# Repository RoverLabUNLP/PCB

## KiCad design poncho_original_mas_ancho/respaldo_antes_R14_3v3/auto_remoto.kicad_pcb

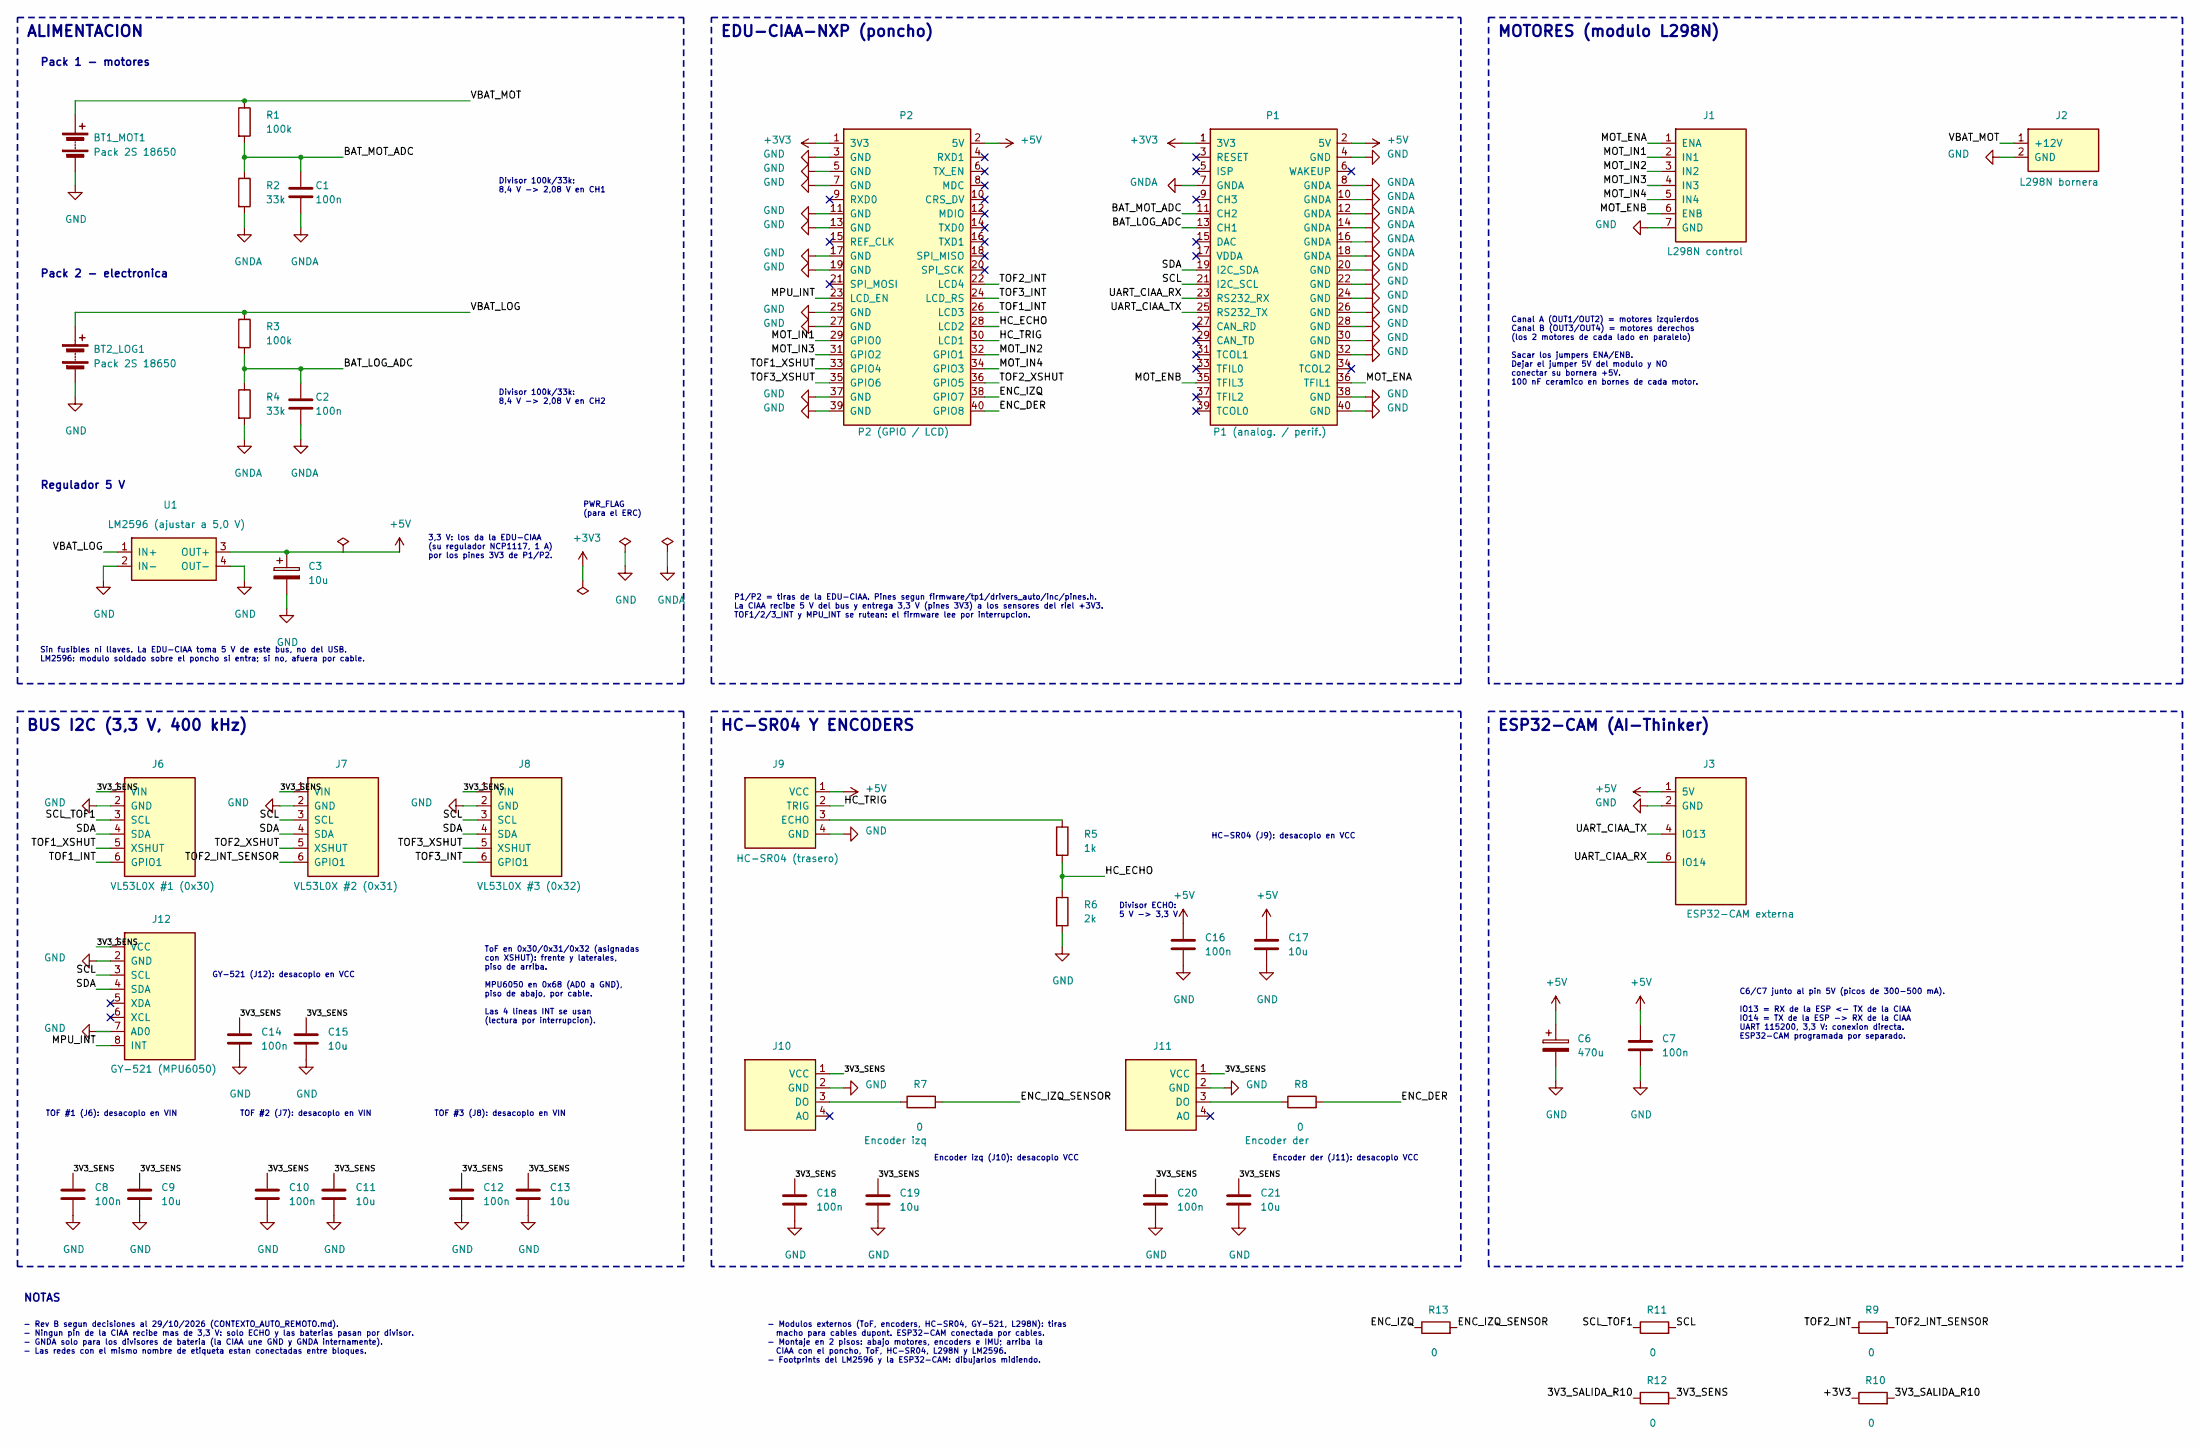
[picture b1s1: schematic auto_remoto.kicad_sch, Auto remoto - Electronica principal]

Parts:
BT1_MOT1, BT2_LOG1: Pack 2S 18650; Bornera_2_P5.00
C1, C2, C7, C8, C10, C12, C14, C16, C18, C20: 100n; C_P5.00
C3: 10u; CP_D6.3_P2.50
C6: 470u; CP_D6.3_P2.50
C9, C11, C13, C15, C17, C19, C21: 10u; C_P5.00
J1: L298N control; Tira_1x07
J2: L298N bornera; Bornera_2_P5.00
J3: ESP32-CAM externa; Pads_ESP32_CAM
J6: VL53L0X #1 (0x30); Tira_1x06
J7: VL53L0X #2 (0x31); Tira_1x06
J8: VL53L0X #3 (0x32); Tira_1x06
J9: HC-SR04 (trasero); Tira_1x04
J10: Encoder izq; Tira_1x04
J11: Encoder der; Tira_1x04
J12: GY-521 (MPU6050); Tira_1x08
P1: P1 (analog. / perif.); Tira_2x20_CIAA_P1
P2: P2 (GPIO / LCD); Tira_2x20_CIAA_P2
R1, R3: 100k; R_P10.16
R2, R4: 33k; R_P10.16
R5: 1k; R_P10.16
R6: 2k; R_P10.16
R7, R8, R9, R10, R11, R12, R13: 0; R_P10.16
U1: LM2596 (ajustar a 5,0 V); Modulo_LM2596

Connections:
+3V3: P1.1 (3V3), P2.1 (3V3), R10.1
+5V: C3.1, C6.1, C7.1, C16.1, C17.1, J3.1 (5V), J9.1 (VCC), P1.2 (5V), P2.2 (5V), U1.3 (OUT+)
/3V3_SALIDA_R10: R10.2, R12.1
/3V3_SENS: C8.1, C9.1, C10.1, C11.1, C12.1, C13.1, C14.1, C15.1, C18.1, C19.1, C20.1, C21.1, J6.1 (VIN), J7.1 (VIN), J8.1 (VIN), J10.1 (VCC), J11.1 (VCC), J12.1 (VCC), R12.2
/BAT_LOG_ADC: C2.1, P1.13 (CH1), R3.2, R4.1
/BAT_MOT_ADC: C1.1, P1.11 (CH2), R1.2, R2.1
/ENC_DER: P2.40 (GPIO8), R8.2
/ENC_IZQ: P2.38 (GPIO7), R13.1
/ENC_IZQ_SENSOR: R7.2, R13.2
/HC_ECHO: P2.28 (LCD2), R5.2, R6.1
/HC_TRIG: J9.2 (TRIG), P2.30 (LCD1)
/MOT_ENA: J1.1 (ENA), P1.36 (TFIL1)
/MOT_ENB: J1.6 (ENB), P1.35 (TFIL3)
/MOT_IN1: J1.2 (IN1), P2.29 (GPIO0)
/MOT_IN2: J1.3 (IN2), P2.32 (GPIO1)
/MOT_IN3: J1.4 (IN3), P2.31 (GPIO2)
/MOT_IN4: J1.5 (IN4), P2.34 (GPIO3)
/MPU_INT: J12.8 (INT), P2.23 (LCD_EN)
/SCL: J7.3 (SCL), J8.3 (SCL), J12.3 (SCL), P1.21 (I2C_SCL), R11.2
/SCL_TOF1: J6.3 (SCL), R11.1
/SDA: J6.4 (SDA), J7.4 (SDA), J8.4 (SDA), J12.4 (SDA), P1.19 (I2C_SDA)
/TOF1_INT: J6.6 (GPIO1), P2.26 (LCD3)
/TOF1_XSHUT: J6.5 (XSHUT), P2.33 (GPIO4)
/TOF2_INT: P2.22 (LCD4), R9.1
/TOF2_INT_SENSOR: J7.6 (GPIO1), R9.2
/TOF2_XSHUT: J7.5 (XSHUT), P2.36 (GPIO5)
/TOF3_INT: J8.6 (GPIO1), P2.24 (LCD_RS)
/TOF3_XSHUT: J8.5 (XSHUT), P2.35 (GPIO6)
/UART_CIAA_RX: J3.6 (IO14), P1.23 (RS232_RX)
/UART_CIAA_TX: J3.4 (IO13), P1.25 (RS232_TX)
/VBAT_LOG: BT2_LOG1.1 (+), R3.1, U1.1 (IN+)
/VBAT_MOT: BT1_MOT1.1 (+), J2.1 (+12V), R1.1
GND: BT1_MOT1.2 (-), BT2_LOG1.2 (-), C3.2, C6.2, C7.2, C8.2, C9.2, C10.2, C11.2, C12.2, C13.2, C14.2, C15.2, C16.2, C17.2, C18.2, C19.2, C20.2, C21.2, J1.7 (GND), J2.2 (GND), J3.2 (GND), J6.2 (GND), J7.2 (GND), J8.2 (GND), J9.4 (GND), J10.2 (GND), J11.2 (GND), J12.2 (GND), J12.7 (AD0), P1.4 (GND), P1.20 (GND), P1.22 (GND), P1.24 (GND), P1.26 (GND), P1.28 (GND), P1.30 (GND), P1.32 (GND), P1.38 (GND), P1.40 (GND), P2.3 (GND), P2.5 (GND), P2.7 (GND), P2.11 (GND), P2.13 (GND), P2.17 (GND), P2.19 (GND), P2.25 (GND), P2.27 (GND), P2.37 (GND), P2.39 (GND), R6.2, U1.2 (IN-), U1.4 (OUT-)
GNDA: C1.2, C2.2, P1.7 (GNDA), P1.8 (GNDA), P1.10 (GNDA), P1.12 (GNDA), P1.14 (GNDA), P1.16 (GNDA), P1.18 (GNDA), R2.2, R4.2
unnamed: J9.3 (ECHO), R5.1
unnamed: J10.3 (DO), R7.1
unnamed: J11.3 (DO), R8.1

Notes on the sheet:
Encoder izq (J10): desacoplo VCC
Regulador 5 V
HC-SR04 (J9): desacoplo en VCC
MOTORES (modulo L298N)
Pack 2 - electronica
ESP32-CAM (AI-Thinker)
HC-SR04 Y ENCODERS
GY-521 (J12): desacoplo en VCC
Divisor 100k/33k: 8,4 V -> 2,08 V en CH1
PWR_FLAG (para el ERC)
Encoder der (J11): desacoplo VCC
Sin fusibles ni llaves. La EDU-CIAA toma 5 V de este bus, no del USB. LM2596: modulo soldado sobre el poncho si entra; si no, afuera por cable.
BUS I2C (3,3 V, 400 kHz)
TOF #3 (J8): desacoplo en VIN
Pack 1 - motores
3,3 V: los da la EDU-CIAA (su regulador NCP1117, 1 A) por los pines 3V3 de P1/P2.
TOF #2 (J7): desacoplo en VIN
C6/C7 junto al pin 5V (picos de 300-500 mA). IO13 = RX de la ESP <- TX de la CIAA IO14 = TX de la ESP -> RX de la CIAA UART 115200, 3,3 V: conexion directa. ESP32-CAM programada por separado.
EDU-CIAA-NXP (poncho)
- Rev B segun decisiones al 29/10/2026 (CONTEXTO_AUTO_REMOTO.md). - Ningun pin de la CIAA recibe mas de 3,3 V: solo ECHO y las baterias pasan por divisor. - GNDA solo para los divisores de bateria (la CIAA une GND y GNDA internamente). - Las redes con el mismo nombre de etiqueta estan conectadas en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
NOTAS
ALIMENTACION
Divisor ECHO: 5 V -> 3,3 V
P1/P2 = tiras de la EDU-CIAA. Pines segun firmware/tp1/drivers_auto/inc/pines.h. La CIAA recibe 5 V del bus y entrega 3,3 V (pines 3V3) a los sensores del riel +3V3. TOF1/2/3_INT y MPU_INT se rutean: el firmware lee por interrupcion.
- Modulos externos (ToF, encoders, HC-SR04, GY-521, L298N): tiras macho para cables dupont. ESP32-CAM conectada por cables. - Montaje en 2 pisos: abajo motores, encoders e IMU; arriba la CIAA con el poncho, ToF, HC-SR04, L298N y LM2596. - Footprints del LM2596 y la ESP32-CAM: dibujarlos midiendo.
TOF #1 (J6): desacoplo en VIN
Divisor 100k/33k: 8,4 V -> 2,08 V en CH2
Canal A (OUT1/OUT2) = motores izquierdos Canal B (OUT3/OUT4) = motores derechos (los 2 motores de cada lado en paralelo) Sacar los jumpers ENA/ENB. Dejar el jumper 5V del modulo y NO conectar su bornera +5V. 100 nF ceramico en bornes de cada motor.
ToF en 0x30/0x31/0x32 (asignadas con XSHUT): frente y laterales, piso de arriba. MPU6050 en 0x68 (AD0 a GND), piso de abajo, por cable. Las 4 lineas INT se usan (lectura por interrupcion).

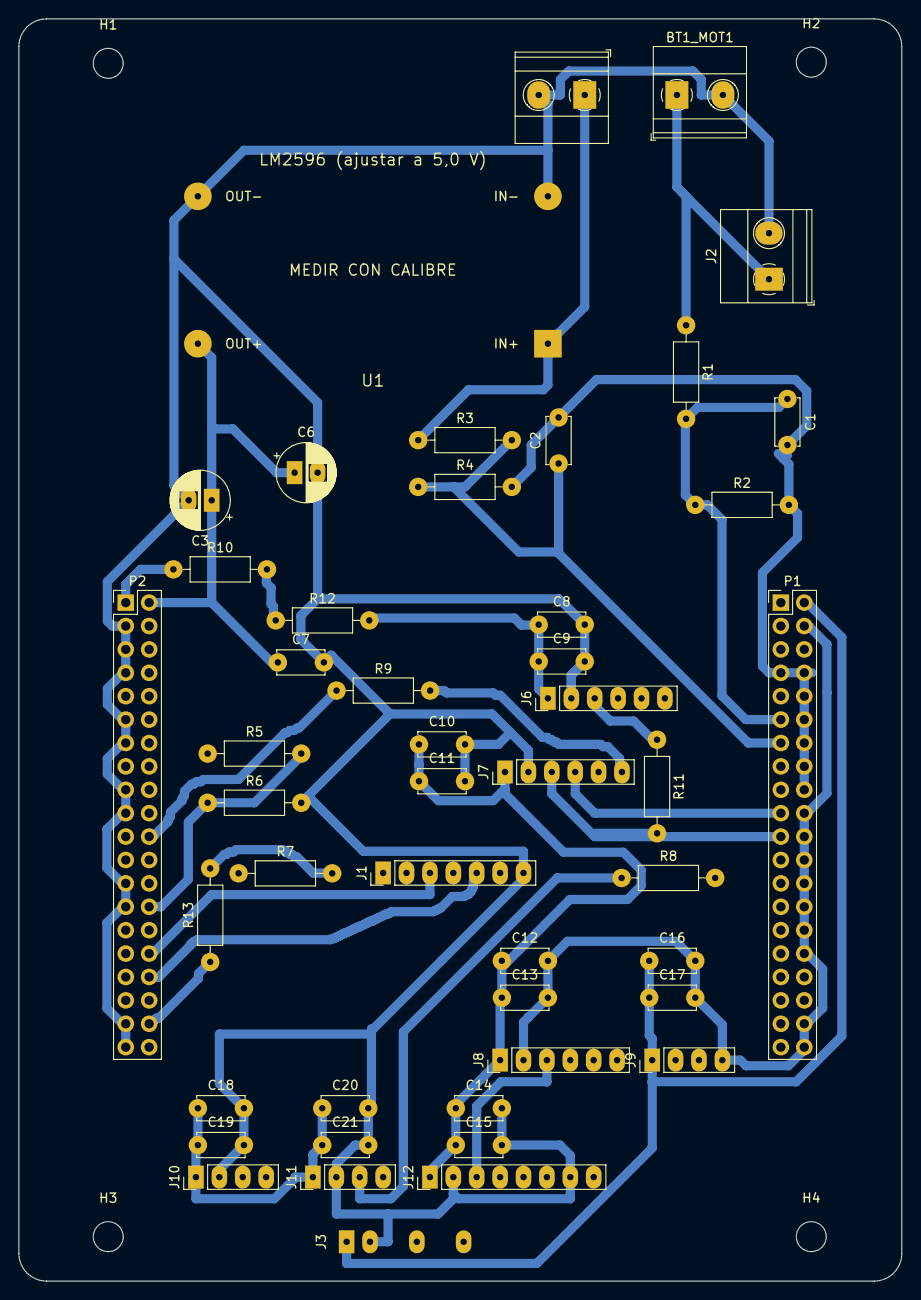
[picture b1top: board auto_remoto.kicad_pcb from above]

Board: 2 copper layers, 95.9 x 137.0 mm, 51 parts (0 on the bottom side), 37 nets.

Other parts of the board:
H1, H2, H3, H4: M3; Agujero_M3
